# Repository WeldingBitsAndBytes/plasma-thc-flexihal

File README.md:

# WIP

A THC control board that can connect to a Expatria Flexihal for controlling a plasma cutter

I've highlighted BOMs for each major component, but I've left some things like hookup wires,
pins, etc to your own design and in particular your own plasma cutter.

## THC Divider Board

`thc_divider_board` directory contains a Kicad PCB designed to isolate the raw plasma cutter 
measurements from the MCU. The PCBs were designed with Oshpark in mind, in particular the
"After Dark" style just for fun. As such, there is minimal silkscreening.

The board is intended to be powered by an internal 24VDC power supply within the plasma cutter. The 
plasma cutter's power supply is protected by a 6KVDC reinforced DC-DC converter. The low-side of the 
isolation amplifier is powered by another isolation DC-DC converter fed from the main DC-DC 
converter. This secondary 5V DC-DC converter also provides power for the MCU.

The MCU is intended to be something like an Arduino Micro which has the correct differential ADC hardware.

## Voltage Sender

`voltage_sender` contains the sketch for the Arduino Micro. The Micro is supported as it can do differential ADC measurements

The signal is connected to the ADC. The MCU is connected to a https://www.dfrobot.com/product-2588.html 
UART Fibre Optic Transceiver

BOM:

| Part    | Quantity | Notes |
| -------- | ------- | ----- |
| Arduino Micro | 1 | |
| UART Fiber Optic Transceiver | 1 | https://www.dfrobot.com/product-2588.html |
| Arduino Nano Screw Terminal Adapter | 1 | https://store-usa.arduino.cc/products/nano-screw-terminal is really nice |
| SC Fibre Optic Cable | 1 | Recommend duplex so you can fire a relay for plasma control |

## Teensy Quadrature Encoder

The `teensy_quadrature_encoder` directory contains the sketch for a Teensy 4 to convert from
serial to quadrature encoding. The Teensy 4 was chosen for its high speed and ability to measure nanoseconds 
for precise timings.  The quadrature encoding is then used to interface with a Expatria FlexiHAL and by 
extension LinuxCNC for torch height control. Similarly, this Teensy will also have a UART Fibre Optic 
Transceiver to talk to the Micro

BOM:

| Part    | Quantity | Notes |
| -------- | ------- | ----- |
| Teensy 4 | 1 | |
| UART Fiber Optic Transceiver | 1 | https://www.dfrobot.com/product-2588.html |
| Screw terminals | 8 | Have enough screw terminals for the uart serial, and power output, and quadrature encoder output |

## FlexiHAL Hookup and Configuration

BOM:

| Part    | Quantity | Notes |
| -------- | ------- | ----- |
| Ethernet cable, TIA 568B straight-through | 1 | |
| Flexihal! | 1 | Duh |

More to come :)

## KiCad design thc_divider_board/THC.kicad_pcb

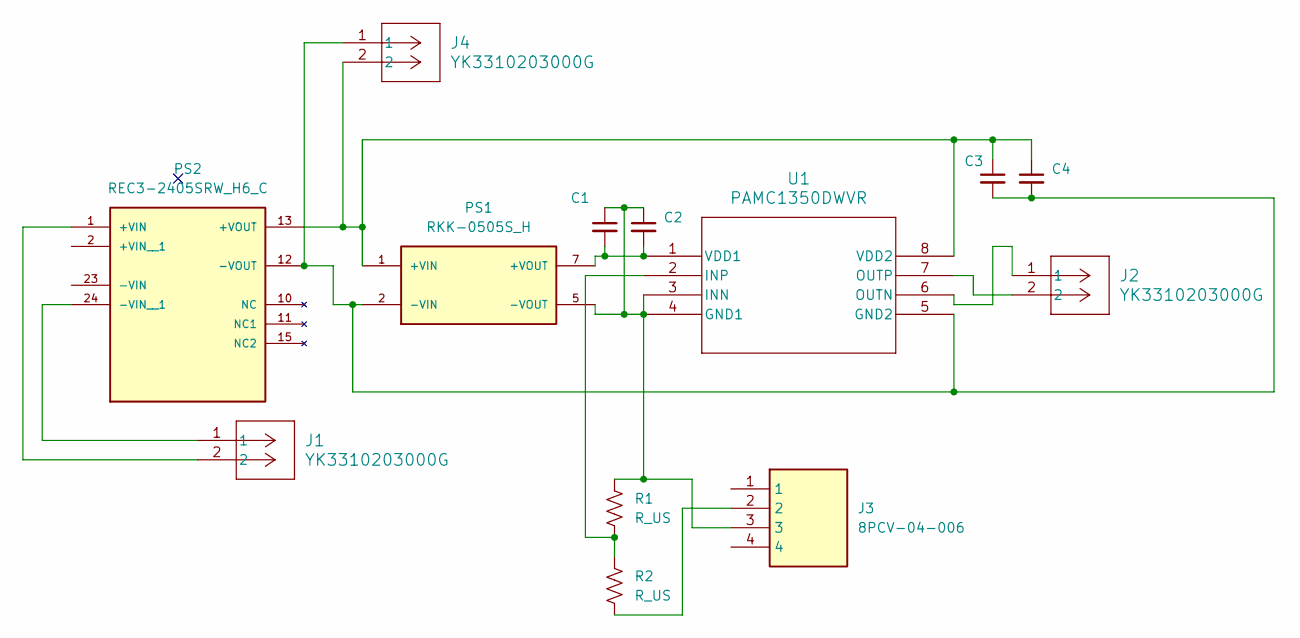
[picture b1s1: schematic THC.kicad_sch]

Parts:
C1, C2, C3, C4: C_Small; CAP_R7540_TDK
J1, J2, J4: YK3310203000G; CONN_YK331020xx00G_AMP
J3: 8PCV-04-006; SHDR4W114P0X1112_1X4_4628X2032X1956P; Mouser Part Number 571-814376570
PS1: RKK-0505S_H; CONV_RKK-0505S_H; PARTREV 0/2023
PS2: REC3-2405SRW_H6_C; CONV_REC3-2405SRW_H6_C; PARTREV N/A
R1, R2: R_US; R_Axial_Power_L25.0mm_W6.4mm_P30.48mm
U1: PAMC1350DWVR; U_PAMC1350DWVR_TEX

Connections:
unnamed: J3.2, R2.2
unnamed: C3.1, C4.1, J4.2, PS1.1 (+VIN), PS2.13 (+VOUT), U1.8 (VDD2)
unnamed: C1.2, C2.2, PS1.7 (+VOUT), U1.1 (VDD1)
unnamed: C3.2, C4.2, J4.1, PS1.2 (-VIN), PS2.12 (-VOUT), U1.5 (GND2)
unnamed: C1.1, C2.1, J3.3, PS1.5 (-VOUT), R1.1, U1.3 (INN), U1.4 (GND1)
unnamed: J1.2, PS2.1 (+VIN)
unnamed: J1.1, PS2.24 (-VIN__1)
unnamed: R1.2, R2.1, U1.2 (INP)
unnamed: J2.1, U1.6 (OUTN)
unnamed: J2.2, U1.7 (OUTP)

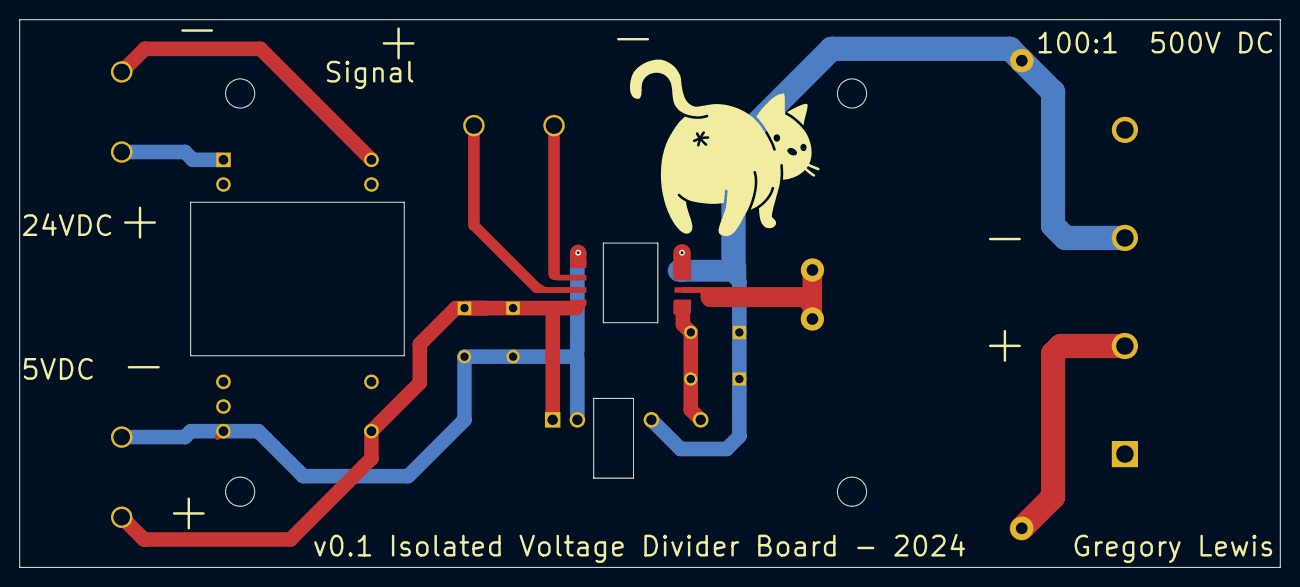
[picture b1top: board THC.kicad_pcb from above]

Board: 2 copper layers, 129.8 x 56.4 mm, 13 parts (0 on the bottom side), 10 nets.

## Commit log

2025-01-28 Create LICENSE
2025-01-28 teensy quadature encoder
2025-01-28 THC board
2025-01-28 readme
2025-01-28 Initial dump of project files (#1)
2025-01-29 add nano voltage sender code
2025-01-29 pretty pictures
2025-01-29 Develop (#2)
2025-01-29 Develop (#3)
2025-01-29 Bom (#4)
2025-03-03 differential ADC
2025-03-03 switch to micro
2025-03-03 Differential adc (#5)
2025-03-03 Update README.md - oops
2025-03-03 Typo in readme (#6)
2025-03-03 more typos
